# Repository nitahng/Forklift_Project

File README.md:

# Forklift_Project 
By Anita Huang

Raspberry-Pi Based Forklift Operation

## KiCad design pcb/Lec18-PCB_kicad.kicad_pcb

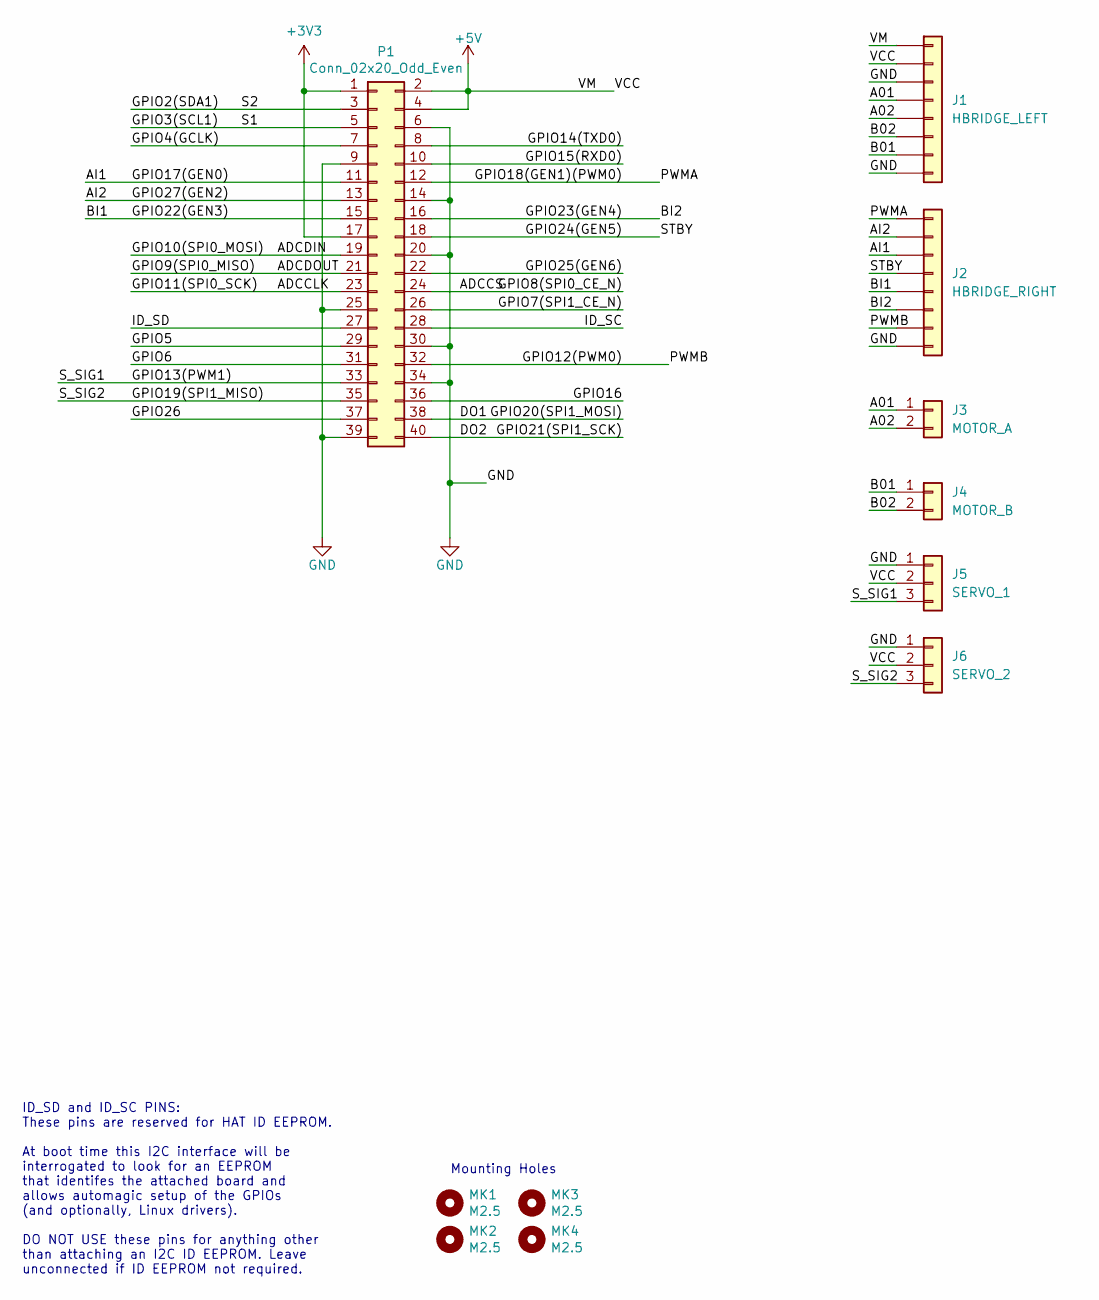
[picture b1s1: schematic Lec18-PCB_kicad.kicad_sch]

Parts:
J1: HBRIDGE_LEFT; PinSocket_1x08_P2.54mm_Vertical
J2: HBRIDGE_RIGHT; PinSocket_1x08_P2.54mm_Vertical
J3: MOTOR_A; PinHeader_1x02_P2.54mm_Vertical
J4: MOTOR_B; PinHeader_1x02_P2.54mm_Vertical
J5: SERVO_1; PinHeader_1x03_P2.54mm_Vertical
J6: SERVO_2; PinHeader_1x03_P2.54mm_Vertical
MK1, MK2, MK3, MK4: M2.5; MountingHole_2.7mm_M2.5
P1: Conn_02x20_Odd_Even; PinSocket_2x20_P2.54mm_Vertical

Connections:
+3V3: P1.1, P1.17
+5V: J1.1, J1.2, J5.2, J6.2, P1.2, P1.4
/A01: J1.4, J3.1
/A02: J1.5, J3.2
/ADCCLK: P1.23
/ADCCS: P1.24
/ADCDIN: P1.19
/ADCDOUT: P1.21
/AI1: J2.3, P1.11
/AI2: J2.2, P1.13
/B01: J1.7, J4.1
/B02: J1.6, J4.2
/BI1: J2.5, P1.15
/BI2: J2.6, P1.16
/DO1: P1.38
/DO2: P1.40
/GPIO2(SDA1): P1.3
/GPIO3(SCL1): P1.5
/GPIO4(GCLK): P1.7
/GPIO5: P1.29
/GPIO6: P1.31
/GPIO7(SPI1_CE_N): P1.26
/GPIO12(PWM0): J2.7, P1.32
/GPIO13(PWM1): J5.3, P1.33
/GPIO14(TXD0): P1.8
/GPIO15(RXD0): P1.10
/GPIO16: P1.36
/GPIO18(GEN1)(PWM0): J2.1, P1.12
/GPIO19(SPI1_MISO): J6.3, P1.35
/GPIO24(GEN5): J2.4, P1.18
/GPIO25(GEN6): P1.22
/GPIO26: P1.37
/ID_SC: P1.28
/ID_SD: P1.27
GND: J1.3, J1.8, J2.8, J5.1, J6.1, P1.6, P1.9, P1.14, P1.20, P1.25, P1.30, P1.34, P1.39

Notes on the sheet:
ID_SD and ID_SC PINS: These pins are reserved for HAT ID EEPROM. At boot time this I2C interface will be interrogated to look for an EEPROM that identifes the attached board and allows automagic setup of the GPIOs (and optionally, Linux drivers). DO NOT USE these pins for anything other than attach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
Mounting Holes

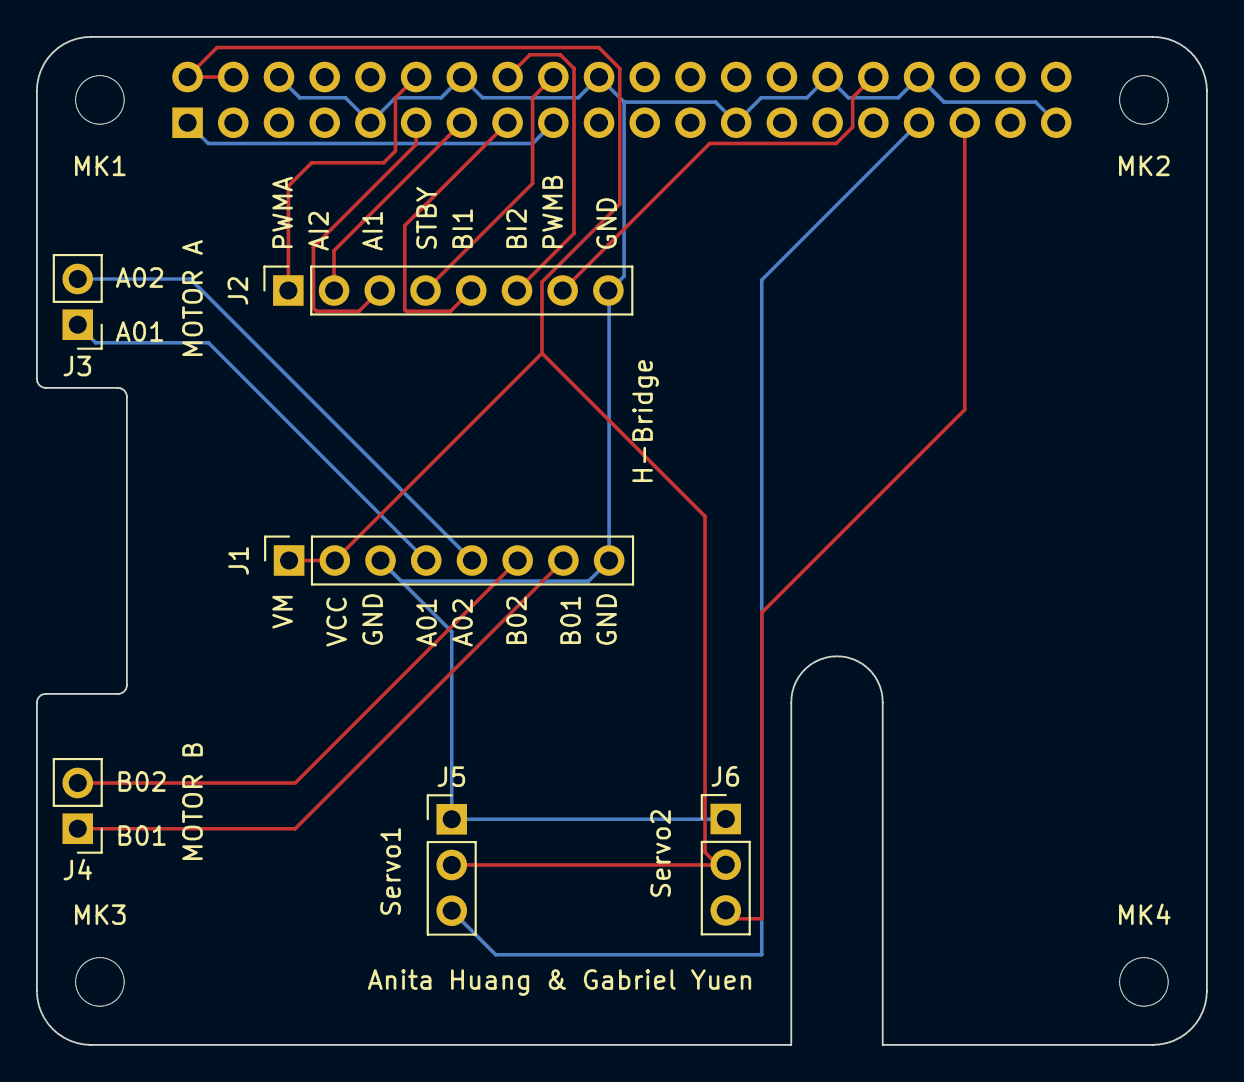
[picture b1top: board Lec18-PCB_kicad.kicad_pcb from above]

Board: 2 copper layers, 65.0 x 56.0 mm, 11 parts (1 on the bottom side), 16 nets.

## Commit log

2026-04-28 ReadME update
2026-04-28 shell
2026-04-28 classes created
2026-04-28 gitignores
2026-04-29 basic PC to Pi commands
2026-04-30 Controllable Car
2026-05-01 Fork Lift
2026-05-04 Integrated Second Socket
2026-05-08 Autonomous push
